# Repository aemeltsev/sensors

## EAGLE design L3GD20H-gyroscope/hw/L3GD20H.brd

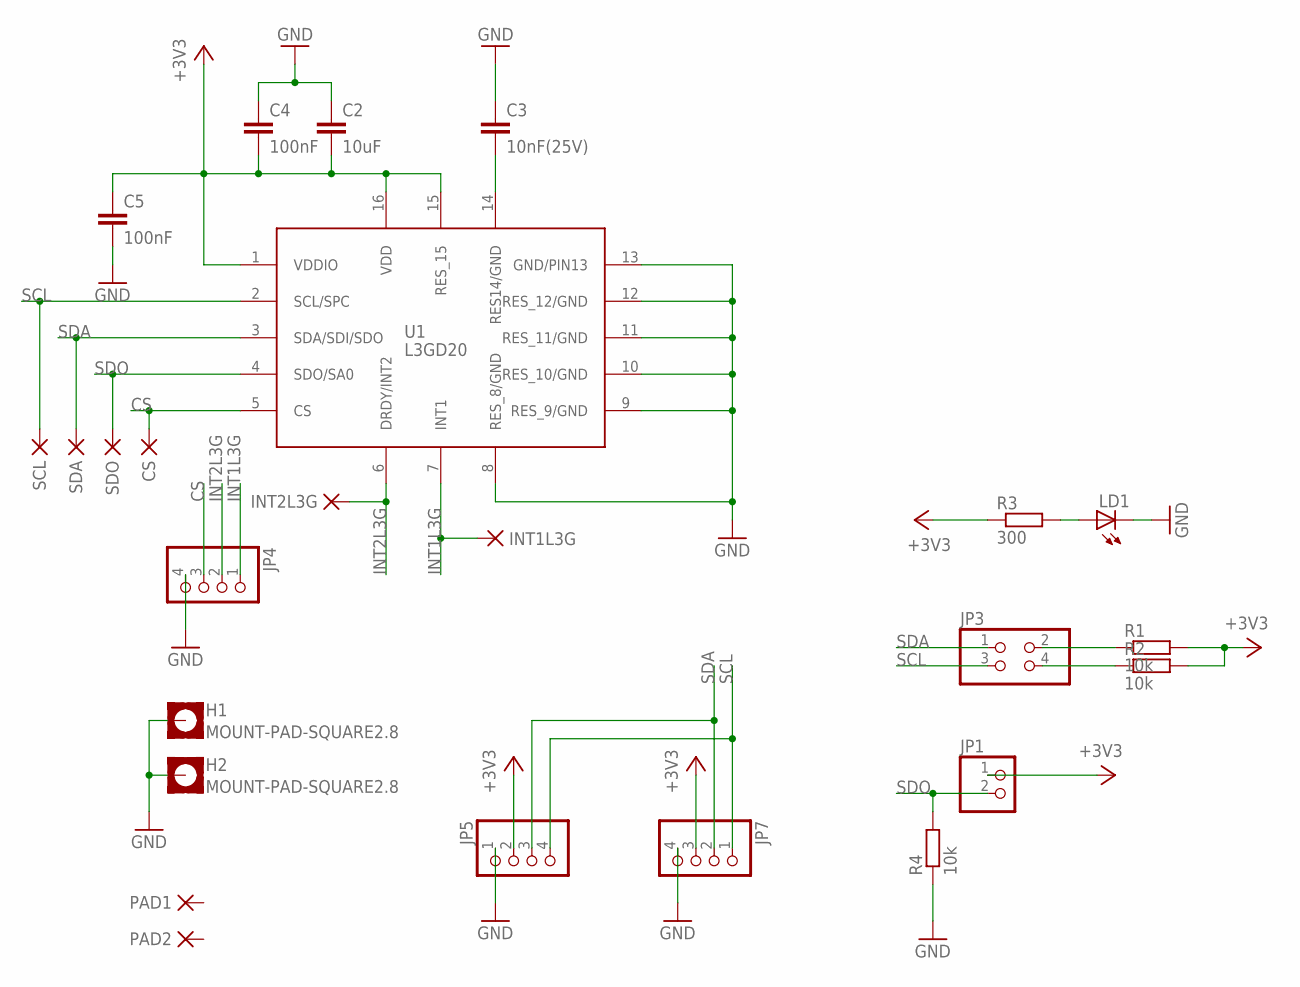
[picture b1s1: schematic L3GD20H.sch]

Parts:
C2: 10uF; C0805
C3: 10nF(25V); C0805
C4, C5: 100nF; C0805
CS: PAD-SMD10R; SMD10R
H1, H2: MOUNT-PAD-SQUARE2.8; 2,8-PAD-SQUARE
INT1L3G, INT2L3G: PAD-SMD10R; SMD10R
JP1: PINHD-1X2; 1X02
JP3: PINHD-2X2_2.54; 2X02
JP4: PINHD-1X4; 1X04
JP5, JP7: PINHD-1X4_2.54-90°; 1X04/90
LD1: LEDCHIPLED_0805; CHIPLED_0805
PAD1, PAD2: PAD-SMD10R; SMD10R
R1, R2, R4: 10k; R0805
R3: 300; R0805
SCL: PAD-SMD10R; SMD10R
SDA: PAD-SMD10R; SMD10R
SDO: PAD-SMD10R; SMD10R
U1: L3GD20; LGA16R65P4X4_400X400X160

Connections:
+3V3: C2.2, C4.2, C5.1, JP1.1, JP5.2, JP7.3, R1.2, R2.2, R3.1, U1.1 (VDDIO), U1.15 (RES_15), U1.16 (VDD)
CS: CS.PAD, JP4.3, U1.5 (CS)
GND: C2.1, C3.1, C4.1, C5.2, H1.B2,8, H2.B2,8, JP4.4, JP5.1, JP7.4, LD1.C, R4.1, U1.8 (RES_8/GND), U1.9 (RES_9/GND), U1.10 (RES_10/GND), U1.11 (RES_11/GND), U1.12 (RES_12/GND), U1.13 (GND/PIN13)
INT1L3G: INT1L3G.PAD, JP4.1, U1.7 (INT1)
INT2L3G: INT2L3G.PAD, JP4.2, U1.6 (DRDY/INT2)
unnamed: JP3.2, R1.1
unnamed: C3.2, U1.14 (RES14/GND)
unnamed: JP3.4, R2.1
unnamed: LD1.A, R3.2
SCL: JP3.3, JP5.4, JP7.1, SCL.PAD, U1.2 (SCL/SPC)
SDA: JP3.1, JP5.3, JP7.2, SDA.PAD, U1.3 (SDA/SDI/SDO)
SDO: JP1.2, R4.2, SDO.PAD, U1.4 (SDO/SA0)

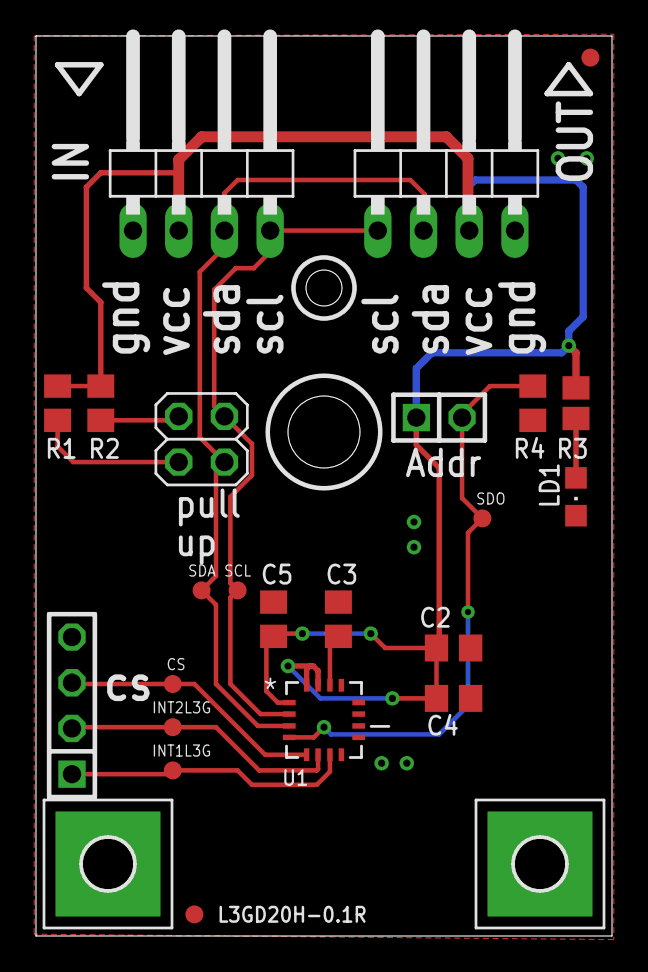
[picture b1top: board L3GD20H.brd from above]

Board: 2 copper layers, 32.0 x 50.0 mm, 25 parts (0 on the bottom side), 12 nets.

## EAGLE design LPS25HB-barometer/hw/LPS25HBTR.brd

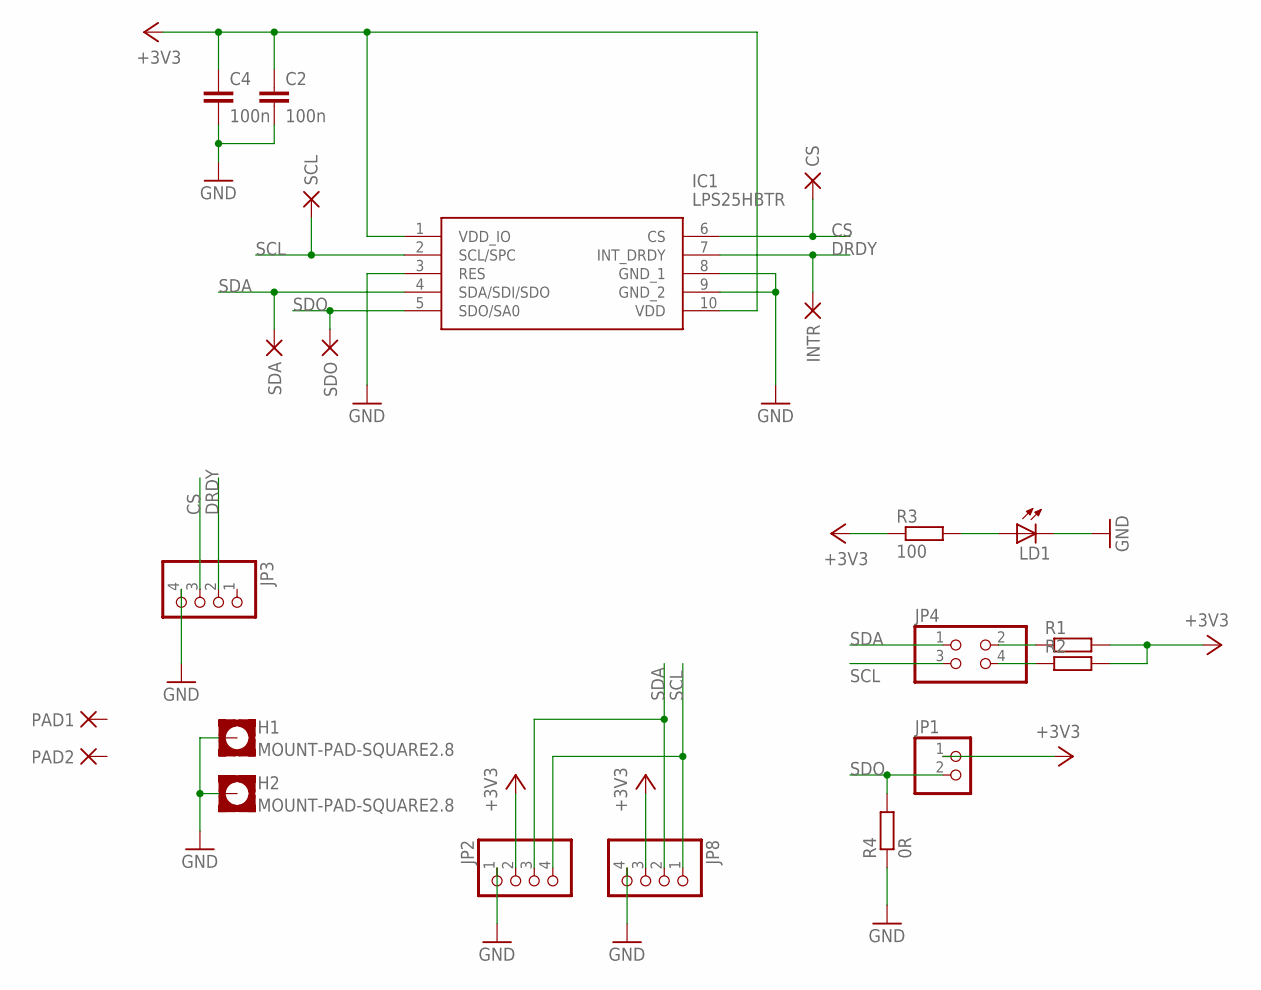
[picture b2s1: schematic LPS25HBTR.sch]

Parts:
C2, C4: 100n; C0805
CS: PAD-SMD10R; SMD10R
H1, H2: MOUNT-PAD-SQUARE2.8; 2,8-PAD-SQUARE
IC1: LPS25HBTR; PQFN60P250X250X80-10N
INTR: PAD-SMD10R; SMD10R
JP1: PINHD-1X2; 1X02
JP2, JP8: PINHD-1X4_2.54-90°; 1X04/90
JP3: PINHD-1X4; 1X04
JP4: PINHD-2X2_2.54; 2X02
LD1: LEDCHIPLED_0805; CHIPLED_0805
PAD1, PAD2: PAD-SMD10R; SMD10R
R1, R2: R-EU_R0805; R0805
R3: 100; R0805
R4: 0R; R0805
SCL: PAD-SMD10R; SMD10R
SDA: PAD-SMD10R; SMD10R
SDO: PAD-SMD10R; SMD10R

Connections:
+3V3: C2.1, C4.1, IC1.1 (VDD_IO), IC1.10 (VDD), JP1.1, JP2.2, JP8.3, R1.2, R2.2, R3.1
CS: CS.PAD, IC1.6 (CS), JP3.3
DRDY: IC1.7 (INT_DRDY), INTR.PAD, JP3.2
GND: C2.2, C4.2, H1.B2,8, H2.B2,8, IC1.3 (RES), IC1.8 (GND_1), IC1.9 (GND_2), JP2.1, JP3.4, JP8.4, LD1.C, R4.1
unnamed: JP4.2, R1.1
unnamed: LD1.A, R3.2
unnamed: JP4.4, R2.1
SCL: IC1.2 (SCL/SPC), JP2.4, JP4.3, JP8.1, SCL.PAD
SDA: IC1.4 (SDA/SDI/SDO), JP2.3, JP4.1, JP8.2, SDA.PAD
SDO: IC1.5 (SDO/SA0), JP1.2, R4.2, SDO.PAD

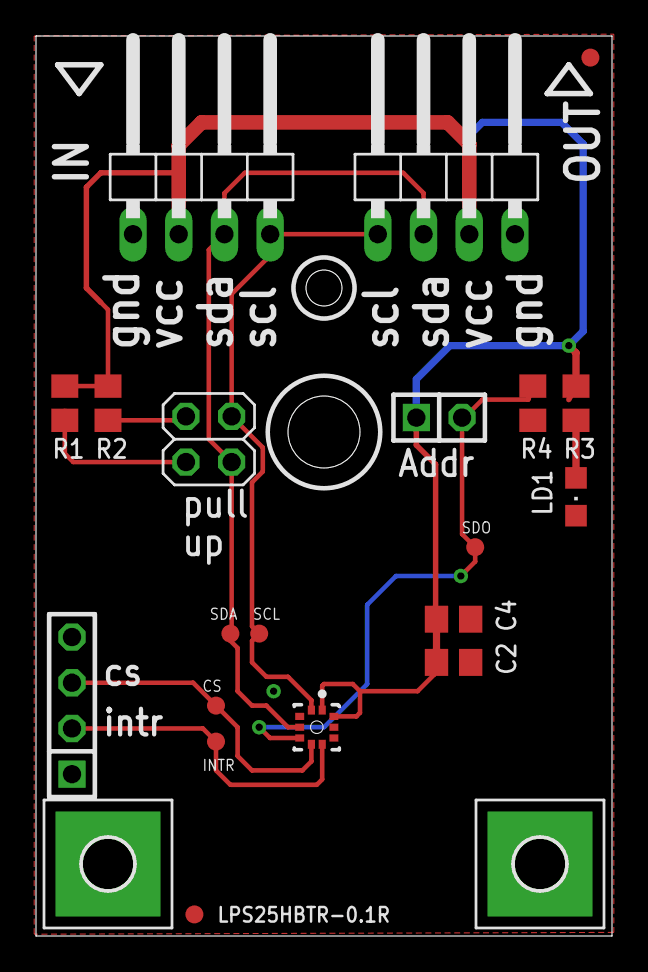
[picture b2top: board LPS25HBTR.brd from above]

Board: 2 copper layers, 32.0 x 50.0 mm, 22 parts (0 on the bottom side), 10 nets.

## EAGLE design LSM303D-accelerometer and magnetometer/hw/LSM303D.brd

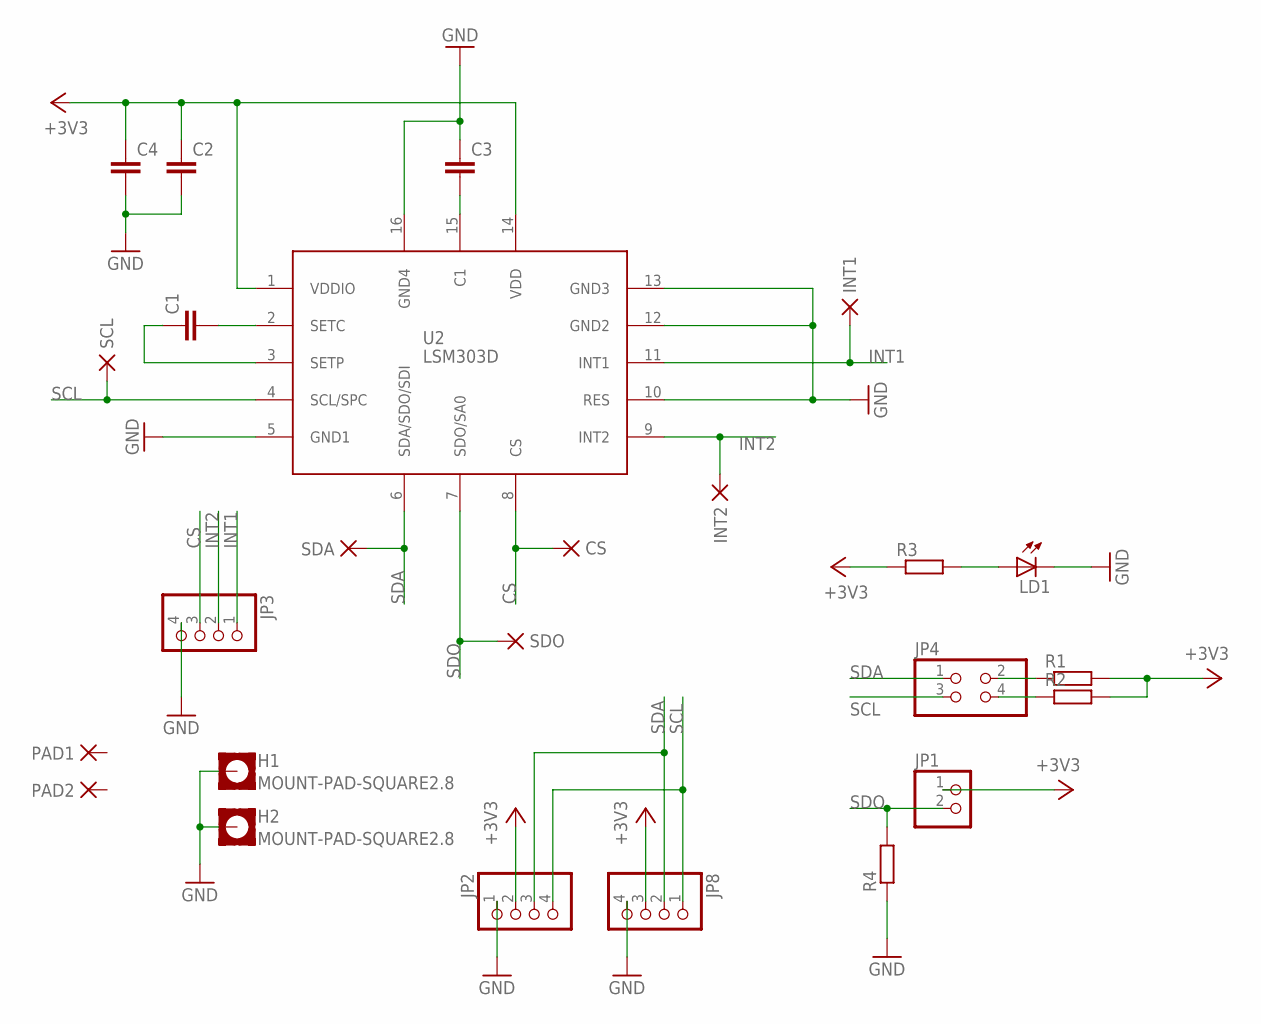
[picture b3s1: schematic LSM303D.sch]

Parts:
C1, C2, C3, C4: C-EUC0805; C0805
CS: PAD-SMD10R; SMD10R
H1, H2: MOUNT-PAD-SQUARE2.8; 2,8-PAD-SQUARE
INT1, INT2: PAD-SMD10R; SMD10R
JP1: PINHD-1X2; 1X02
JP2, JP8: PINHD-1X4_2.54-90°; 1X04/90
JP3: PINHD-1X4; 1X04
JP4: PINHD-2X2_2.54; 2X02
LD1: LEDCHIPLED_0805; CHIPLED_0805
PAD1, PAD2: PAD-SMD10R; SMD10R
R1, R2, R3, R4: R-EU_R0805; R0805
SCL: PAD-SMD10R; SMD10R
SDA: PAD-SMD10R; SMD10R
SDO: PAD-SMD10R; SMD10R
U2: LSM303D; LGA16R50P3X5_300X300X100

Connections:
+3V3: C2.1, C4.1, JP1.1, JP2.2, JP8.3, R1.2, R2.2, R3.1, U2.1 (VDDIO), U2.14 (VDD)
CS: CS.PAD, JP3.3, U2.8 (CS)
GND: C2.2, C3.1, C4.2, H1.B2,8, H2.B2,8, JP2.1, JP3.4, JP8.4, LD1.C, R4.1, U2.5 (GND1), U2.10 (RES), U2.12 (GND2), U2.13 (GND3), U2.16 (GND4)
INT1: INT1.PAD, JP3.1, U2.11 (INT1)
INT2: INT2.PAD, JP3.2, U2.9 (INT2)
unnamed: JP4.2, R1.1
unnamed: C3.2, U2.15 (C1)
unnamed: LD1.A, R3.2
unnamed: JP4.4, R2.1
unnamed: C1.2, U2.2 (SETC)
unnamed: C1.1, U2.3 (SETP)
SCL: JP2.4, JP4.3, JP8.1, SCL.PAD, U2.4 (SCL/SPC)
SDA: JP2.3, JP4.1, JP8.2, SDA.PAD, U2.6 (SDA/SDO/SDI)
SDO: JP1.2, R4.2, SDO.PAD, U2.7 (SDO/SA0)

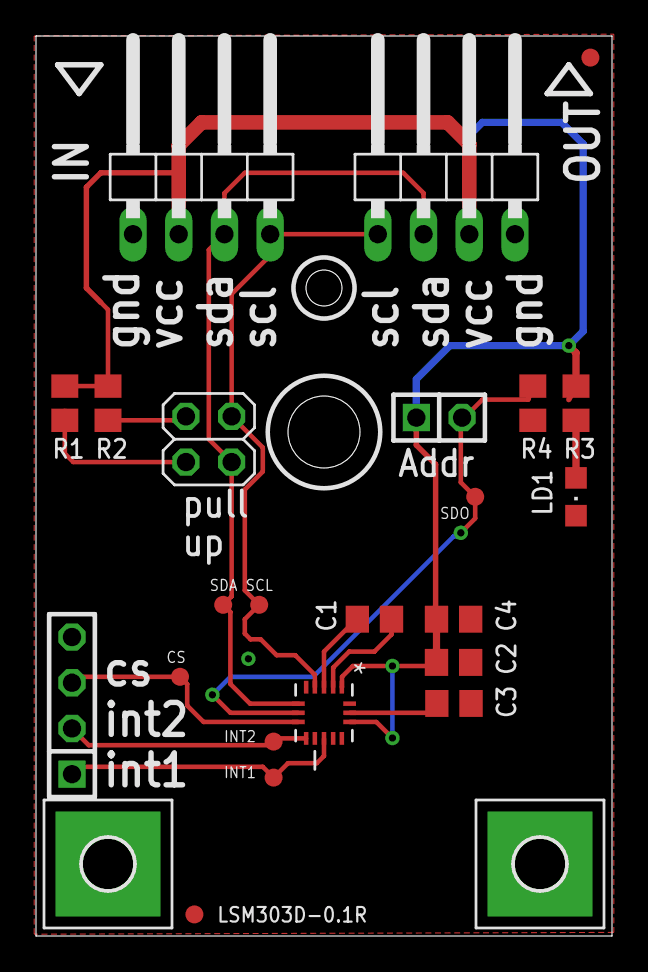
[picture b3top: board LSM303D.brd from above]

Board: 2 copper layers, 32.0 x 50.0 mm, 25 parts (0 on the bottom side), 14 nets.

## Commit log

2019-07-15 Repo
    Create repo
2019-07-15 add hts221
    add hts221 hw and doc
2019-07-16 Create L3GD20 repo
    Add gyro hw files
2019-07-22 add LPS25HB repo
    add LPS25HB repo - hw and doc
2019-07-24 add LSM303D repo
    add LSM303D repo, hw and doc
2020-06-07 add files
    add gerber files, image
2020-06-15 add image
    add image

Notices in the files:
parts and their libraries:
dpads: Copyright (C) 2004, Bob Starr (bobstarr@mindspring.com)
